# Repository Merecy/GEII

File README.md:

# GEII
L'ensemble de mes programmes en GEII, si ça peut vous servir ^^

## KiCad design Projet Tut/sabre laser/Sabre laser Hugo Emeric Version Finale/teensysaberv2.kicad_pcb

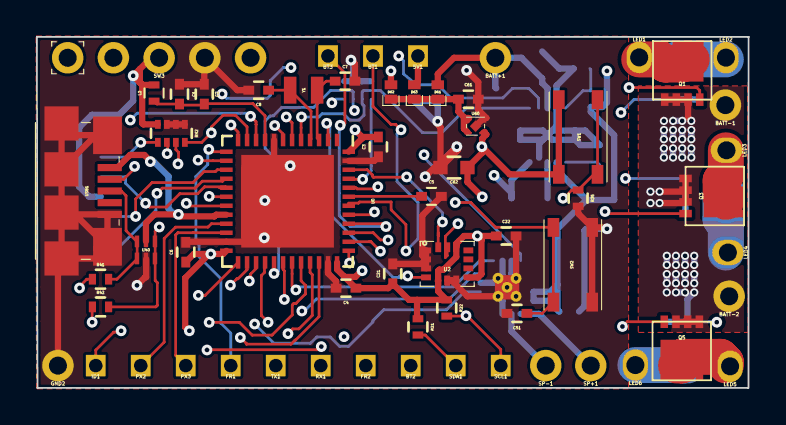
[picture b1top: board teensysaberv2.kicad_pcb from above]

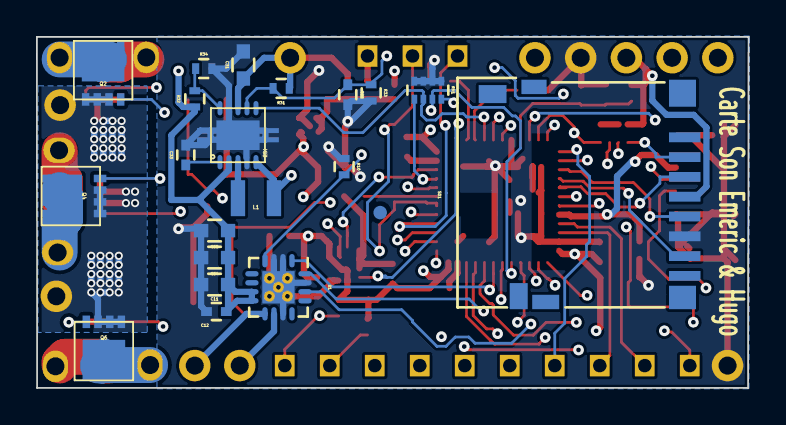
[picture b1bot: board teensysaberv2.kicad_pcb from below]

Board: 4 copper layers, 39.5 x 19.5 mm, 81 parts (21 on the bottom side), 59 nets.

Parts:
5V1: CONN_01X01; 1upin
BATT+1: CONN_01X01; 1pin
BATT-1, BATT-2: CONN_01X01; 1pin
BT1, BT2, BT3: CONN_01X01; 1upin
C1, C61: 1uF; C_0402
C2, C3, C4, C5, C6, C12, C21, C22, C32, C33, C51: 0.1uF; C_0402
C7, C8: 5.6pF; C_0402
C11, C31, C34, C35, C62: 10uF; C_0603
D61, D62, D63: PMEG2005ELD; SOD882D
FR1, FR2: CONN_01X01; 1upin
GND2: CONN_01X01; 1pin
IC3: TPS61200; QFN-10-PAD
ID1: CONN_01X01; 1upin
L1: 4.7 uH 1.2A; 2520
L2: 600 ferrite; L_0402
LED1, LED2, LED3, LED4, LED5, LED6: CONN_01X01; 1pin-oval
PX2, PX3: CONN_01X01; 1upin
Q1, Q2, Q3, Q4, Q5, Q6: Q_NMOS_DGS; DMG7430LFG
R10, R35: 10k; R_0402
R21, R22: 2.2k; R_0402
R31, R32: 2M 1%; R_0402
R33, R34: 220k 1%; R_0402
R41, R42: 22; R_0402
RN1, RN2: 10k; R_Array_Concave_4x0402
RX1: CONN_01X01; 1upin
Ref**: Val**; fiduciary-small
SCL1: CONN_01X01; 1upin
SD1: microsd_socket; DM3D-SF
SDA1: CONN_01X01; 1upin
SP+1: CONN_01X01; 1pin
SP-1: CONN_01X01; 1pin
SW1, SW2: SW_Push; PTS810
SW3: Conn_01x05; 5pin
TX1: CONN_01X01; 1upin
U0: STM32L433CCU6; QFN-48-1EP_7x7mm_Pitch0.5mm
U1: MAX98357A_TQFN; QFN-16-1EP_3x3mm_Pitch0.5mm_ThermalVias
U2: LSM6DS3H; LGA-14L
U40: HSP061-2M6; uQFN6
U60: NCP177; XDFN4
USB1: USB_OTG; 10118192
Y1: ST2012SB 4pF; ST2012SB

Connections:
3.3v: C3.2, C4.1, C6.1, C21.1, C22.1, C62.1, L2.2, R21.1, R22.1, RN2.4, SD1.4, SW1.1, SW3.3, U0.24, U0.36, U0.48, U2.5, U2.8, U2.12, U60.1
5v: 5V1.1, C11.1, C12.1, C34.1, C35.1, D63.2, IC3.2, R32.1, U1.7, U1.8
BATT+: BATT+1.1, C31.1, D61.2, IC3.5, IC3.8, L1.2, R31.1
BATT-: BATT-1.1, BATT-2.1, Q1.3, Q2.3, Q3.3, Q4.3, Q5.3, Q6.3
BTN: R35.1, SW1.2, U0.44
Button1: BT1.1, U0.42
Button2: BT2.1, U0.41
Button3: BT3.1, U0.40
CH1: Q1.2, RN2.8, U0.11
CH2: Q2.2, RN1.7, U0.29
CH3: Q3.2, RN2.7, U0.18
CH4: Q4.2, RN1.8, U0.19
CH5: Q5.2, RN2.6, U0.28
CH6: Q6.2, RN1.5, U0.45
DM: R42.1, U0.32
DP: R41.1, U0.33
FREE1: FR1.1, U0.13
FREE2: FR2.1, U0.39
GND: C1.1, C2.1, C3.1, C4.2, C5.2, C6.2, C7.2, C8.2, C11.2, C12.2, C21.2, C22.2, C31.2, C32.2, C33.2, C34.2, C35.2, C51.2, C61.2, C62.2, GND2.1, IC3.4, IC3.9, IC3.11, IC3.12, IC3.13, IC3.14, IC3.15, R10.2, R33.2, R34.2, R35.2, RN1.1, RN1.2, RN1.3, RN1.4, RN2.1, RN2.2, RN2.3, SD1.6, SW2.1, SW3.4, U0.8, U0.23, U0.35, U0.47, U0.49, U1.2, U1.3, U1.11, U1.15, U1.17, U2.1, U2.2, U2.3, U2.6, U2.7, U40.2, U60.2, U60.5, USB1.5, USB1.6
I2S_BCLK: U0.26, U1.16
I2S_DATA: U0.31, U1.1
I2S_LRCLK: U0.25, U1.14
INT: U0.2, U2.4
unnamed: C1.2, C2.2, L2.1, U0.9
unnamed: C5.1, U0.43
unnamed: C7.1, U0.3, Y1.1
unnamed: C8.1, U0.4, Y1.2
unnamed: C33.1, IC3.1
unnamed: C61.1, D61.1, D62.1, D63.1, U60.3, U60.4
unnamed: IC3.3, L1.1
unnamed: IC3.10, R32.2, R34.1
unnamed: LED1.1, Q1.1
unnamed: LED2.1, Q2.1
unnamed: LED3.1, Q3.1
unnamed: LED4.1, Q4.1
unnamed: LED5.1, Q5.1
unnamed: LED6.1, Q6.1
unnamed: R41.2, U40.1, U40.6, USB1.3
unnamed: R42.2, U40.3, U40.4, USB1.2
unnamed: SP+1.1, U1.9
unnamed: SP-1.1, U1.10
RESET: C51.1, SW2.2, SW3.5, U0.7
RX: RX1.1, U0.38
SCL: R22.2, SCL1.1, U0.30, U2.13
SDA: R21.2, SDA1.1, U0.46, U2.14
SWDCLK: SW3.1, U0.37
SWDIO: SW3.2, U0.34
TX: TX1.1, U0.12
VBUS: D62.2, U0.20, U40.5, USB1.1
amp_en: R10.1, U0.6, U1.4
boost_en: IC3.6, RN1.6, U0.5
id-neopixel_data: ID1.1, U0.10
miso: SD1.7, U0.16
mosi: SD1.3, U0.17
neopixel_data2: PX2.1, U0.21
neopixel_data3: PX3.1, U0.22
sclk: SD1.5, U0.15
sd_en: RN2.5, SD1.2, U0.27
vtest: C32.1, IC3.7, R31.2, R33.1, U0.14

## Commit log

2022-05-25 README.md
2022-05-25 NMEA183 Arduino
    Creation d'une trame NMEA183 sur Arduino, un peu a la bled
2022-05-25 Programme E&R
2022-05-25 Exo Interaction PHP-MySQL
2022-05-25 TP MQTT
2022-05-25 Projet tut
2022-05-25 KiCad File pour le sabre
2022-05-25 Upload Projet debimetre connecte
2022-05-25 Upload Info Embarque S2
2022-05-25 Upload Info Embarque S3
2022-05-25 Upload Mod com sys lin num S3
2022-05-25 Upload Outils logiciel S3
2022-05-25 Upload Outils logiciel S2
2022-05-25 Upload Programmation Oriente Objet S3
2022-05-25 Upload Reseau S3
2022-05-25 Upload Traitement Numerique du Signal
2022-05-25 Upload TP ROBOT S2
